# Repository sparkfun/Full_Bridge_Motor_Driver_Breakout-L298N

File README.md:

SparkFun Breakout Board for L298N Full-Bridge Motor Driver
========================================

[*SparkFun Breakout Board for L298N Full-Bridge Motor Driver (BOB-09540)*](https://www.sparkfun.com/products/9540)

This is a breakout board for the L298N full-bridge dual motor driver; which comes in a staggered, Multiwatt package.
All pins of the L298N are broken out to a 15-pin 0.1" pitch header. Two mounting holes are also provided.

Repository Contents
-------------------

* **/Hardware** - Eagle design files (.brd, .sch)
* **/Production** - Production panel files (.brd)

Documentation
--------------
* **[SparkFun Fritzing repo](https://github.com/sparkfun/Fritzing_Parts)** - Fritzing diagrams for SparkFun products.
* **[SparkFun 3D Model repo](https://github.com/sparkfun/3D_Models)** - 3D models of SparkFun products. 

License Information
-------------------
This product is _**open source**_! 

The **hardware** is released under [Creative Commons ShareAlike 4.0 International](https://creativecommons.org/licenses/by-sa/4.0/).

Please use, reuse, and modify these files as you see fit. Please maintain attribution to SparkFun Electronics and release anything derivative under the same license.

Distributed as-is; no warranty is given.

- Your friends at SparkFun.

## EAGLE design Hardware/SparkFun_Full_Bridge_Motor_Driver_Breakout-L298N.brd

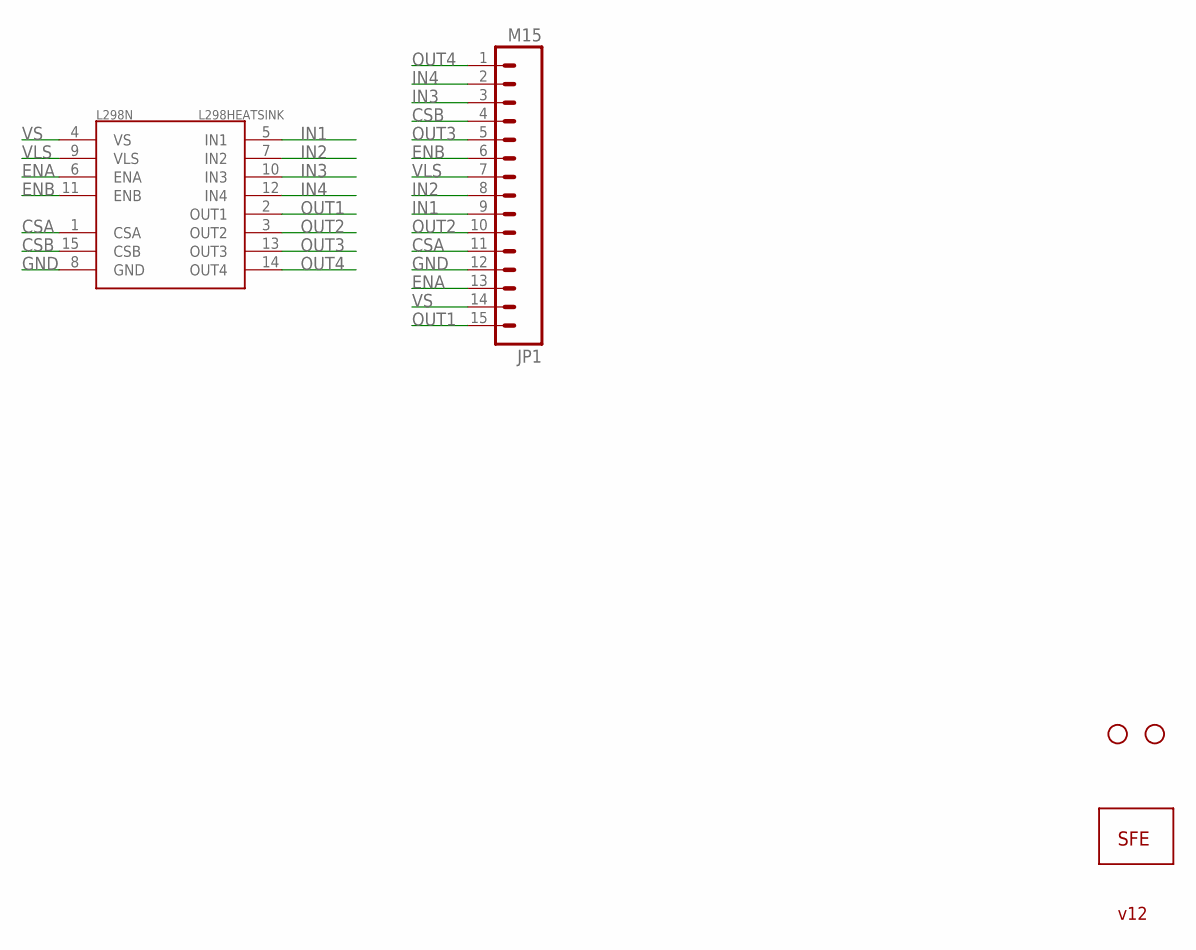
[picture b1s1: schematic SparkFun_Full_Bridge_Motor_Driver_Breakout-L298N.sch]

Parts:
JP1: M15; 1X15
JP2, JP3: STAND-OFF
JP4: LOGO-SFENEW; SFE-NEW-WEBLOGO
L298N: L298HEATSINK; MULTIWATT15_6400BGHEATSINK

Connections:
CSA: JP1.11, L298N.1 (CSA)
CSB: JP1.4, L298N.15 (CSB)
ENA: JP1.13, L298N.6 (ENA)
ENB: JP1.6, L298N.11 (ENB)
GND: JP1.12, L298N.8 (GND)
IN1: JP1.9, L298N.5 (IN1)
IN2: JP1.8, L298N.7 (IN2)
IN3: JP1.3, L298N.10 (IN3)
IN4: JP1.2, L298N.12 (IN4)
OUT1: JP1.15, L298N.2 (OUT1)
OUT2: JP1.10, L298N.3 (OUT2)
OUT3: JP1.5, L298N.13 (OUT3)
OUT4: JP1.1, L298N.14 (OUT4)
VLS: JP1.7, L298N.9 (VLS)
VS: JP1.14, L298N.4 (VS)

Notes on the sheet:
v12

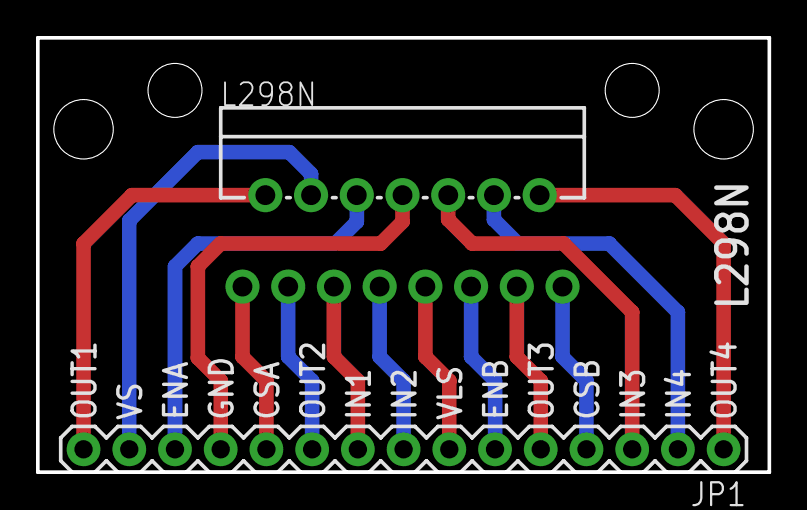
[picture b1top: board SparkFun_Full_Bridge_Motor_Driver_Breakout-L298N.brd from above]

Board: 2 copper layers, 40.6 x 24.1 mm, 5 parts (1 on the bottom side), 15 nets.

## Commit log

2015-05-05 hardware files, readme update
